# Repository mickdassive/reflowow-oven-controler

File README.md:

# reflow-firmware
firmware and hardware for a reflow oven controller. this is verry mutch a WORK IN PROGRESS.

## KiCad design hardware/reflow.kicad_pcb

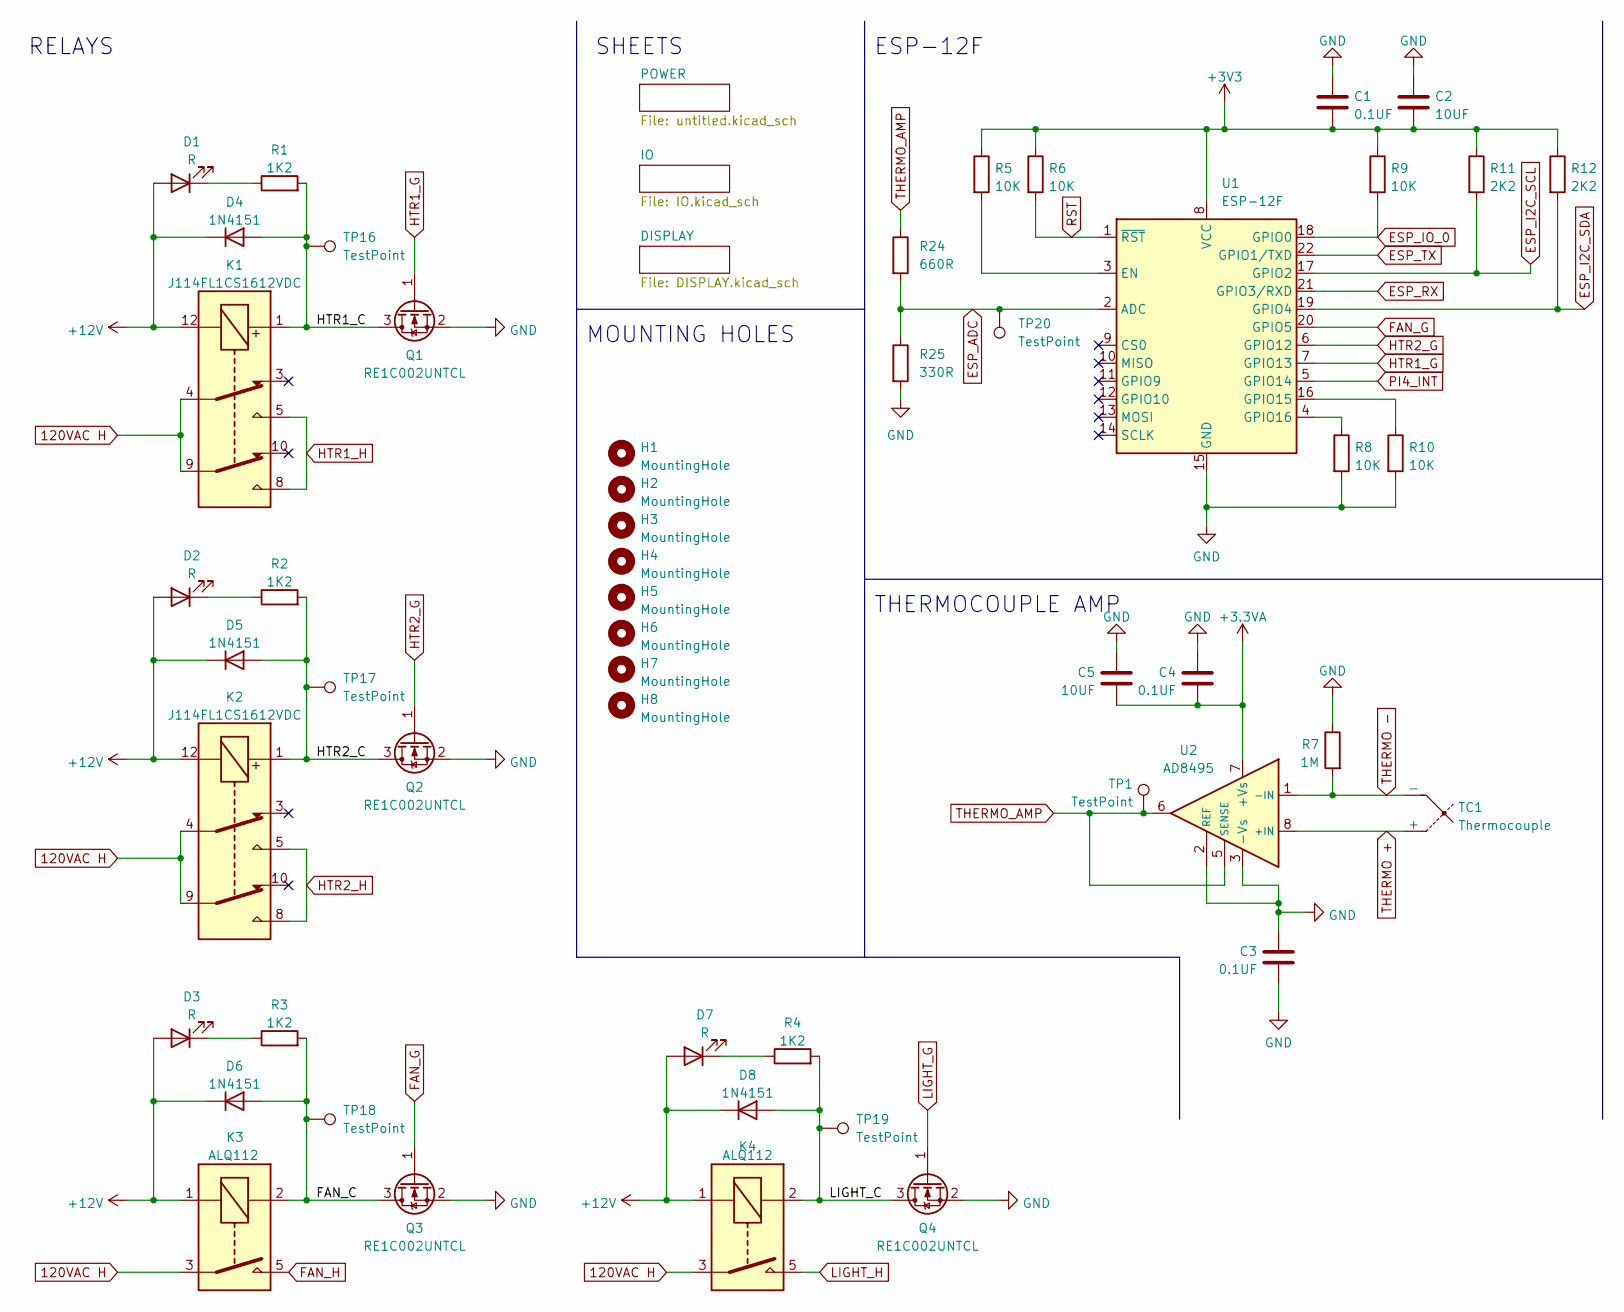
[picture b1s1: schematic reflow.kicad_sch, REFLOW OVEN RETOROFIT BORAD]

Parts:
C1, C3, C4: 0.1UF; C_0603_1608Metric
C2, C5: 10UF; C_0603_1608Metric
D1, D2, D3, D7: R; D_0603_1608Metric
D4, D5, D6, D8: 1N4151; D_0603_1608Metric
H1, H2, H3, H4, H5, H6, H7, H8: MountingHole; MountingHole_3.2mm_M3
K1, K2: J114FL1CS1612VDC
K3, K4: ALQ112; RELAY_ALQ112
Q1, Q2, Q3, Q4: RE1C002UNTCL; SOT-416
R1, R2, R3, R4: 1K2; R_0603_1608Metric
R5, R6, R8, R9, R10: 10K; R_0603_1608Metric
R7: 1M; R_0603_1608Metric
R11, R12: 2K2; R_0603_1608Metric
R24: 660R; R_0603_1608Metric
R25: 330R; R_0603_1608Metric
TC1: Thermocouple
TP1, TP16, TP17, TP18, TP19, TP20: TestPoint; TestPoint_Pad_D2.0mm
U1: ESP-12F; ESP-12E
U2: AD8495; MSOP-8_3x3mm_P0.65mm

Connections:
120VAC H: K1.4, K1.9, K2.4, K2.9, K3.3, K3.14, K4.3, K4.14; also elsewhere on the board
+3.3VA: C4.2, C5.2, U2.7 (+Vs); also elsewhere on the board
+3V3: C1.2, C2.2, R5.1, R6.1, R9.1, R11.1, R12.1, U1.8 (VCC); also elsewhere on the board
+12V: D1.2 (A), D2.2 (A), D3.2 (A), D4.1 (K), D5.1 (K), D6.1 (K), D7.2 (A), D8.1 (K), K1.12, K2.12, K3.1, K4.1; also elsewhere on the board
ESP_ADC: R24.2, R25.1, TP20.1, U1.2 (ADC)
ESP_I2C_SCL: R11.2, U1.17 (GPIO2); also elsewhere on the board
ESP_I2C_SDA: R12.2, U1.19 (GPIO4); also elsewhere on the board
ESP_IO_0: R9.2, U1.18 (GPIO0); also elsewhere on the board
ESP_RX: U1.21 (GPIO3/RXD); also elsewhere on the board
ESP_TX: U1.22 (GPIO1/TXD); also elsewhere on the board
FAN_G: Q3.1 (G), U1.20 (GPIO5)
FAN_H: K3.5, K3.8; also elsewhere on the board
HTR1_G: Q1.1 (G), U1.7 (GPIO13)
HTR1_H: K1.5, K1.8; also elsewhere on the board
HTR2_G: Q2.1 (G), U1.6 (GPIO12)
HTR2_H: K2.5, K2.8; also elsewhere on the board
LIGHT_G: Q4.1 (G); also elsewhere on the board
LIGHT_H: K4.5, K4.8; also elsewhere on the board
unnamed: D1.1 (K), R1.1
unnamed: D2.1 (K), R2.1
unnamed: D3.1 (K), R3.1
unnamed: D7.1 (K), R4.1
unnamed: R5.2, U1.3 (EN)
unnamed: R8.1, U1.4 (GPIO16)
unnamed: R10.1, U1.16 (GPIO15)
PI4_INT: U1.5 (GPIO14); also elsewhere on the board
RST: R6.2, U1.1 (~RST); also elsewhere on the board
THERMO +: TC1.1 (+), U2.8 (+IN); also elsewhere on the board
THERMO -: R7.2, TC1.2 (-), U2.1 (-IN); also elsewhere on the board
THERMO_AMP: R24.1, TP1.1, U2.5 (SENSE), U2.6

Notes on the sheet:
THERMOCOUPLE AMP
ESP-12F
SHEETS
MOUNTING HOLES
RELAYS

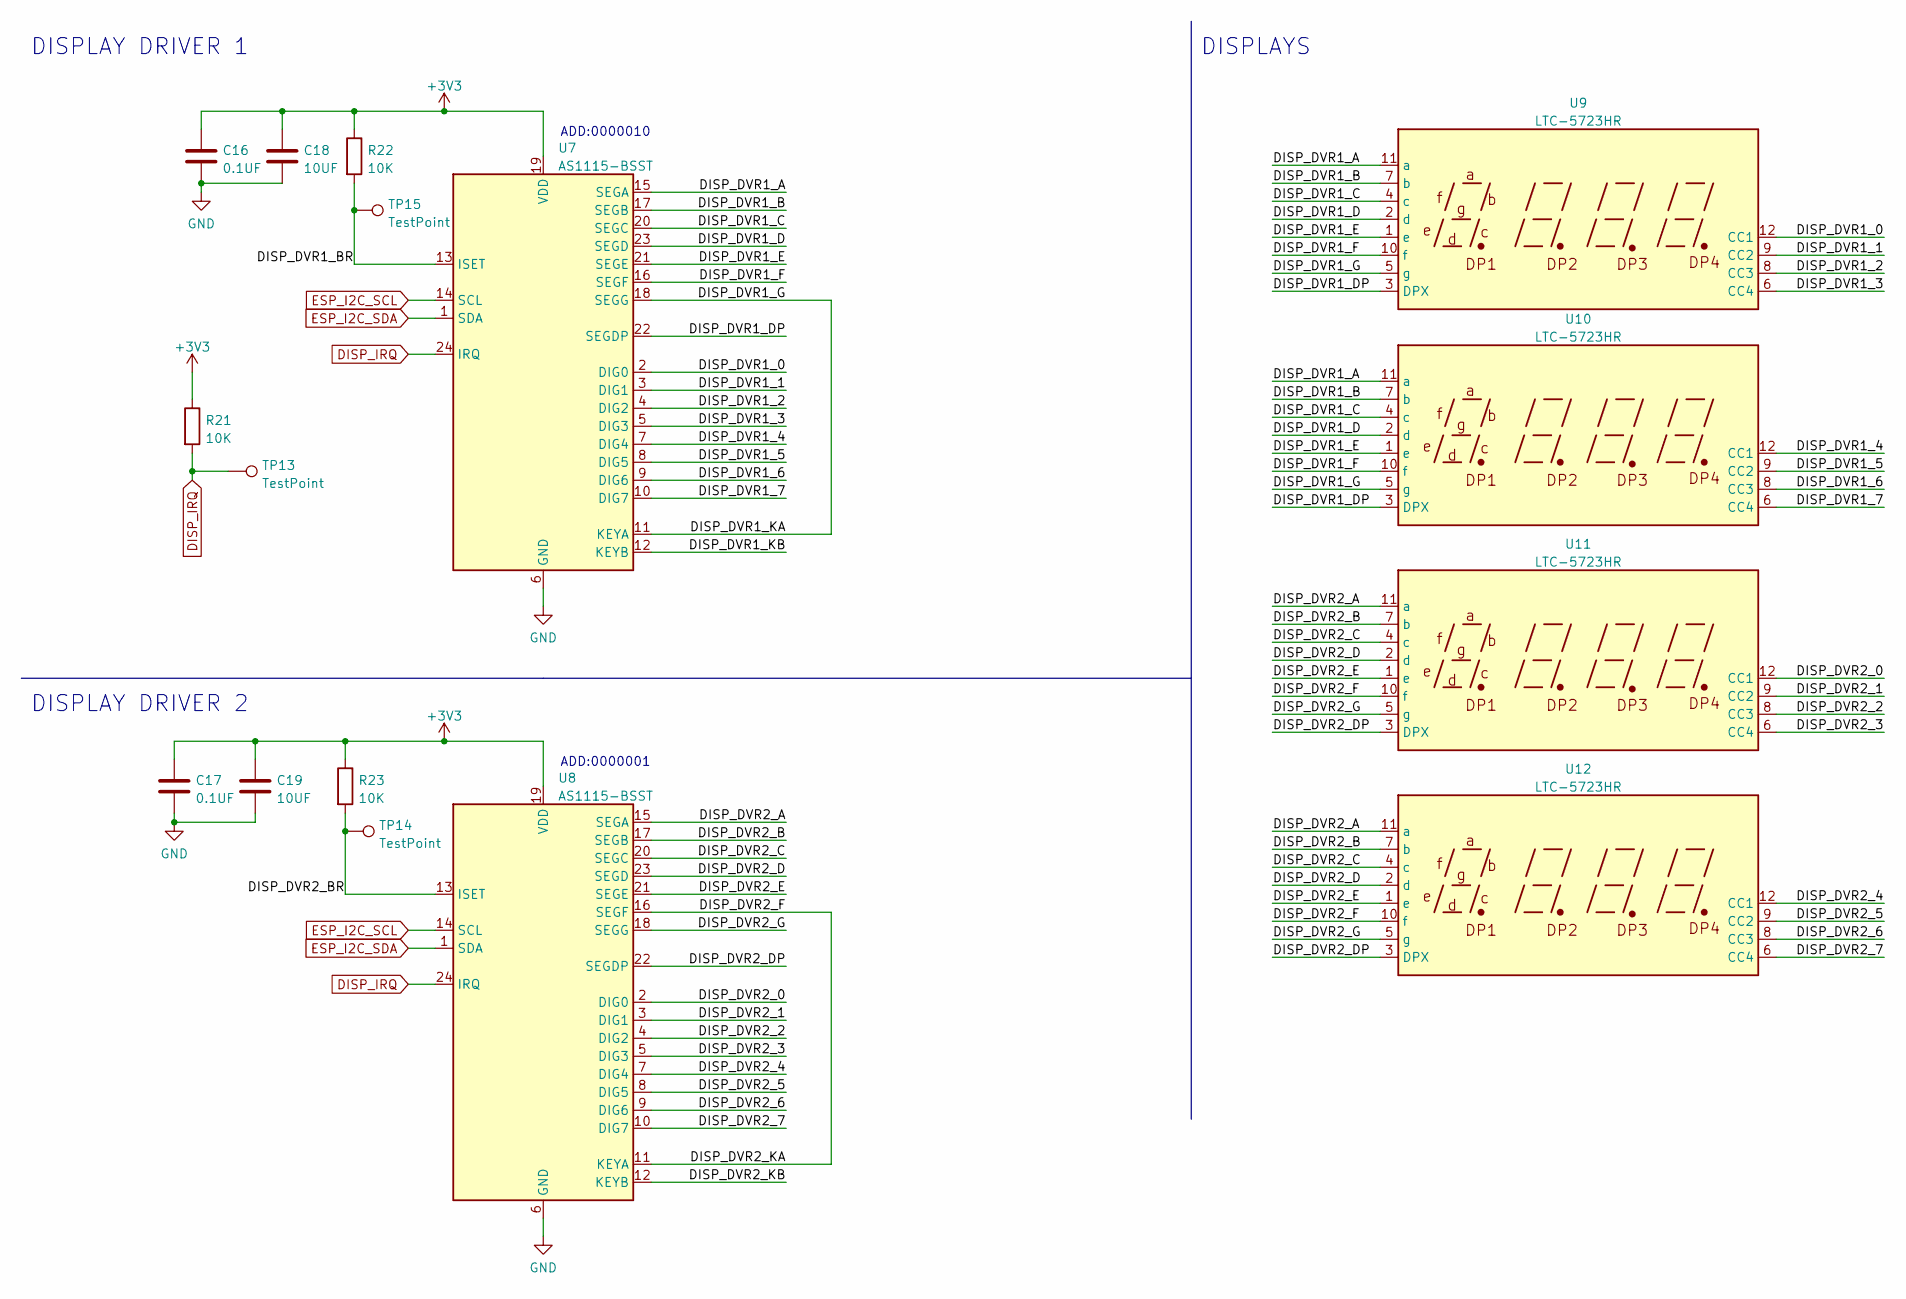
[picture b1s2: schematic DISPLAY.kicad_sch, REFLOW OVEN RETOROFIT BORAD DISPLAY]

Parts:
C16, C17: 0.1UF; C_0603_1608Metric
C18, C19: 10UF; C_0603_1608Metric
R21, R22, R23: 10K; R_0603_1608Metric
TP13, TP14, TP15: TestPoint; TestPoint_Pad_D2.0mm
U7, U8: AS1115-BSST; QSOP-24_3.9x8.7mm_P0.635mm
U9, U10, U11, U12: LTC-5723HR; CA56-12CGKWA

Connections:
+3V3: C16.1, C17.1, C18.1, C19.1, R21.1, R22.1, R23.1, U7.19 (VDD), U8.19 (VDD); also elsewhere on the board
/DISPLAY/DISP_DVR1_0: U7.2 (DIG0), U9.12 (CC1)
/DISPLAY/DISP_DVR1_1: U7.3 (DIG1), U9.9 (CC2)
/DISPLAY/DISP_DVR1_2: U7.4 (DIG2), U9.8 (CC3)
/DISPLAY/DISP_DVR1_3: U7.5 (DIG3), U9.6 (CC4)
/DISPLAY/DISP_DVR1_4: U7.7 (DIG4), U10.12 (CC1)
/DISPLAY/DISP_DVR1_5: U7.8 (DIG5), U10.9 (CC2)
/DISPLAY/DISP_DVR1_6: U7.9 (DIG6), U10.8 (CC3)
/DISPLAY/DISP_DVR1_7: U7.10 (DIG7), U10.6 (CC4)
/DISPLAY/DISP_DVR1_A: U7.15 (SEGA), U9.11 (a), U10.11 (a)
/DISPLAY/DISP_DVR1_B: U7.17 (SEGB), U9.7 (b), U10.7 (b)
/DISPLAY/DISP_DVR1_BR: R22.2, TP15.1, U7.13 (ISET)
/DISPLAY/DISP_DVR1_C: U7.20 (SEGC), U9.4 (c), U10.4 (c)
/DISPLAY/DISP_DVR1_D: U7.23 (SEGD), U9.2 (d), U10.2 (d)
/DISPLAY/DISP_DVR1_DP: U7.22 (SEGDP), U9.3 (DPX), U10.3 (DPX)
/DISPLAY/DISP_DVR1_E: U7.21 (SEGE), U9.1 (e), U10.1 (e)
/DISPLAY/DISP_DVR1_F: U7.16 (SEGF), U9.10 (f), U10.10 (f)
/DISPLAY/DISP_DVR1_G: U7.11 (KEYA), U7.18 (SEGG), U9.5 (g), U10.5 (g)
/DISPLAY/DISP_DVR1_KB: U7.12 (KEYB)
/DISPLAY/DISP_DVR2_0: U8.2 (DIG0), U11.12 (CC1)
/DISPLAY/DISP_DVR2_1: U8.3 (DIG1), U11.9 (CC2)
/DISPLAY/DISP_DVR2_2: U8.4 (DIG2), U11.8 (CC3)
/DISPLAY/DISP_DVR2_3: U8.5 (DIG3), U11.6 (CC4)
/DISPLAY/DISP_DVR2_4: U8.7 (DIG4), U12.12 (CC1)
/DISPLAY/DISP_DVR2_5: U8.8 (DIG5), U12.9 (CC2)
/DISPLAY/DISP_DVR2_6: U8.9 (DIG6), U12.8 (CC3)
/DISPLAY/DISP_DVR2_7: U8.10 (DIG7), U12.6 (CC4)
/DISPLAY/DISP_DVR2_A: U8.15 (SEGA), U11.11 (a), U12.11 (a)
/DISPLAY/DISP_DVR2_B: U8.17 (SEGB), U11.7 (b), U12.7 (b)
/DISPLAY/DISP_DVR2_BR: R23.2, TP14.1, U8.13 (ISET)
/DISPLAY/DISP_DVR2_C: U8.20 (SEGC), U11.4 (c), U12.4 (c)
/DISPLAY/DISP_DVR2_D: U8.23 (SEGD), U11.2 (d), U12.2 (d)
/DISPLAY/DISP_DVR2_DP: U8.22 (SEGDP), U11.3 (DPX), U12.3 (DPX)
/DISPLAY/DISP_DVR2_E: U8.21 (SEGE), U11.1 (e), U12.1 (e)
/DISPLAY/DISP_DVR2_F: U8.11 (KEYA), U8.16 (SEGF), U11.10 (f), U12.10 (f)
/DISPLAY/DISP_DVR2_G: U8.18 (SEGG), U11.5 (g), U12.5 (g)
/DISPLAY/DISP_DVR2_KB: U8.12 (KEYB)
DISP_IRQ: R21.2, TP13.1, U7.24 (IRQ), U8.24 (IRQ)
ESP_I2C_SCL: U7.14 (SCL), U8.14 (SCL); also elsewhere on the board
ESP_I2C_SDA: U7.1 (SDA), U8.1 (SDA); also elsewhere on the board

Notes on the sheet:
DISPLAYS
DISPLAY DRIVER 2
ADD:0000001
ADD:0000010
DISPLAY DRIVER 1

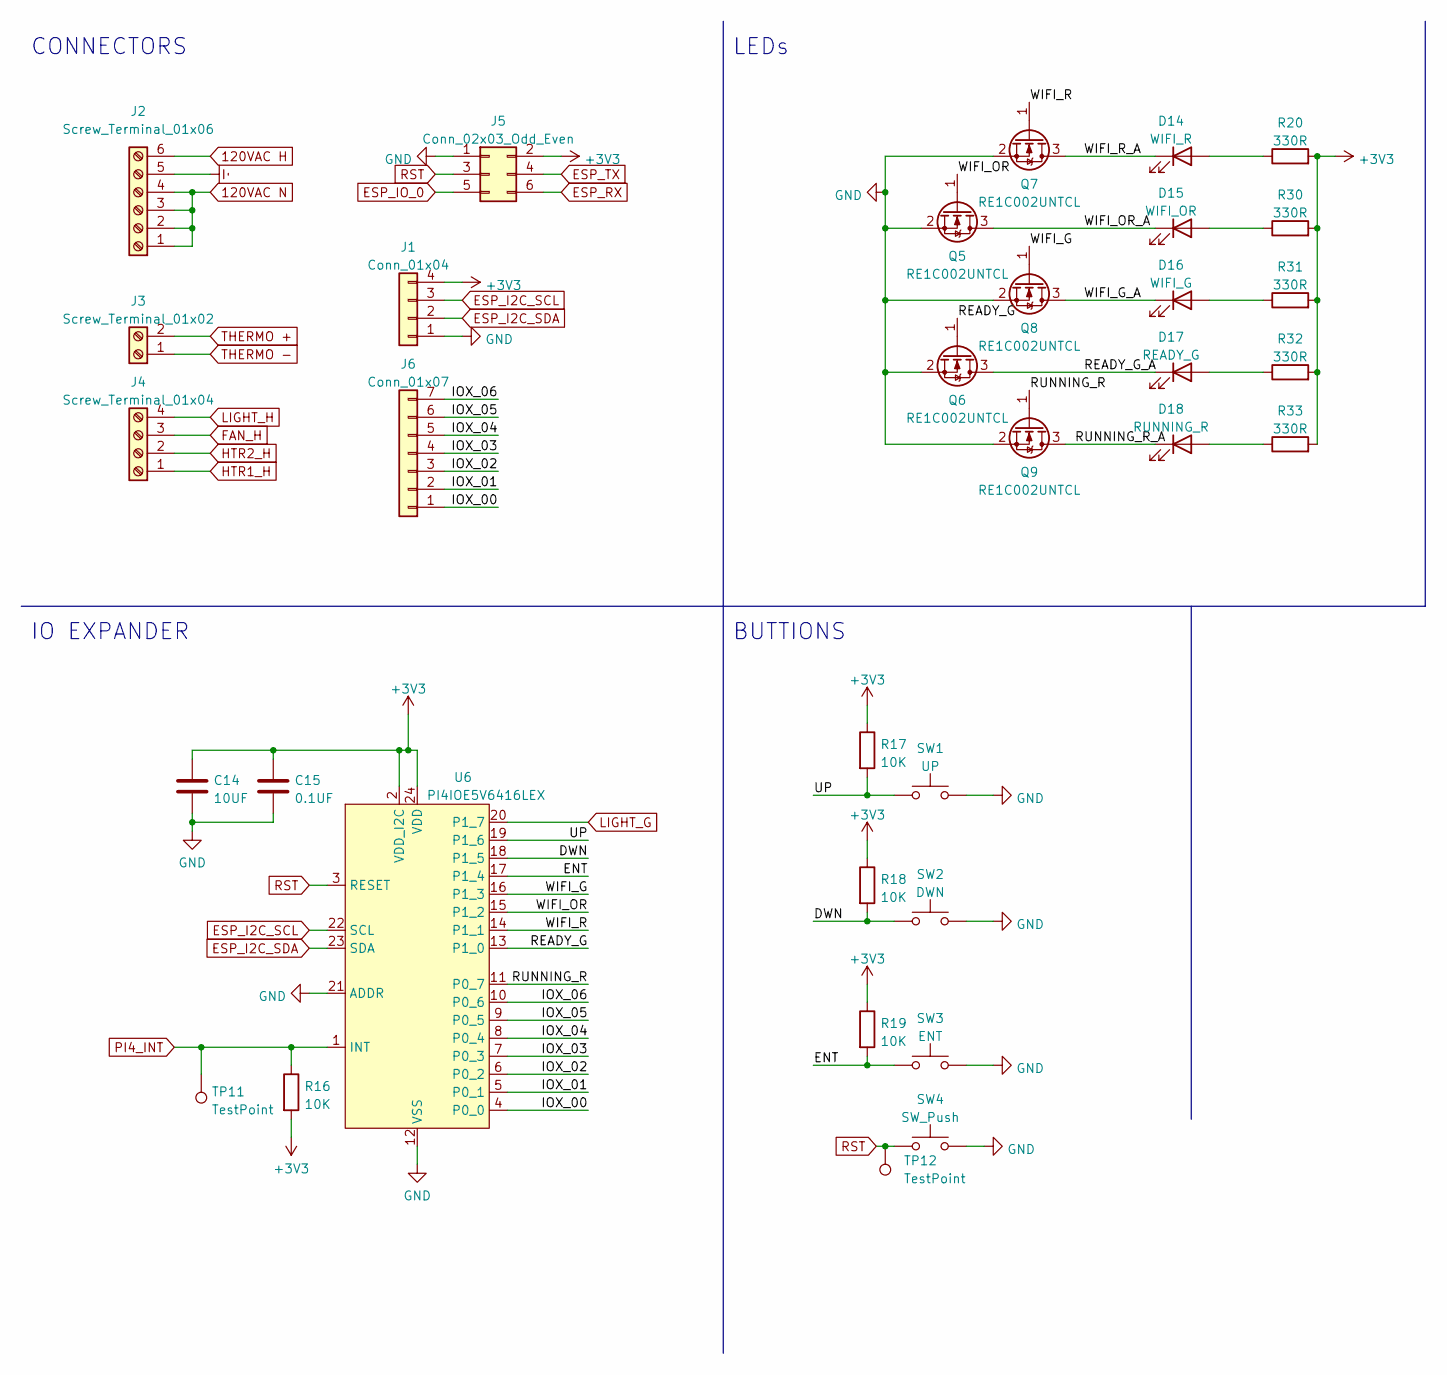
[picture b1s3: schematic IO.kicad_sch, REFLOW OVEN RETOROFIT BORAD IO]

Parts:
C14: 10UF; C_0603_1608Metric
C15: 0.1UF; C_0603_1608Metric
D14: WIFI_R; D_0603_1608Metric
D15: WIFI_OR; D_0603_1608Metric
D16: WIFI_G; D_0603_1608Metric
D17: READY_G; D_0603_1608Metric
D18: RUNNING_R; D_0603_1608Metric
J1: Conn_01x04; PinHeader_1x04_P2.54mm_Vertical
J2: Screw_Terminal_01x06; SCREW_TERM_5MM_7
J3: Screw_Terminal_01x02; SCREW_TERM_5MM_2
J4: Screw_Terminal_01x04; SCREW_TERM_5MM_4
J5: Conn_02x03_Odd_Even; PinHeader_2x03_P2.54mm_Vertical
J6: Conn_01x07; PinHeader_1x07_P2.54mm_Vertical
Q5, Q6, Q7, Q8, Q9: RE1C002UNTCL; SOT-416
R16, R17, R18, R19: 10K; R_0603_1608Metric
R20, R30, R31, R32, R33: 330R; R_0603_1608Metric
SW1: UP; SW_Cherry_MX_1.00u_PCB
SW2: DWN; SW_Cherry_MX_1.00u_PCB
SW3: ENT; SW_Cherry_MX_1.00u_PCB
SW4: SW_Push; SW_Cherry_MX_1.00u_PCB
TP11, TP12: TestPoint; TestPoint_Pad_D2.0mm
U6: PI4IOE5V6416LEX; TSSOP-24_4.4x7.8mm_P0.65mm

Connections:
120VAC H: J2.7; also elsewhere on the board
120VAC N: J2.1, J2.2, J2.3, J2.4; also elsewhere on the board
+3V3: C14.1, C15.1, J1.4, J5.2, R16.2, R17.1, R18.1, R19.1, R20.2, R30.2, R31.2, R32.2, R33.2, U6.2 (VDD_I2C), U6.24 (VDD); also elsewhere on the board
/IO/DWN: R18.2, SW2.1, U6.18 (P1_5)
/IO/ENT: R19.2, SW3.1, U6.17 (P1_4)
/IO/IOX_00: J6.1, U6.4 (P0_0)
/IO/IOX_01: J6.2, U6.5 (P0_1)
/IO/IOX_02: J6.3, U6.6 (P0_2)
/IO/IOX_03: J6.4, U6.7 (P0_3)
/IO/IOX_04: J6.5, U6.8 (P0_4)
/IO/IOX_05: J6.6, U6.9 (P0_5)
/IO/IOX_06: J6.7, U6.10 (P0_6)
/IO/READY_G: Q6.1 (G), U6.13 (P1_0)
/IO/RUNNING_R: Q9.1 (G), U6.11 (P0_7)
/IO/UP: R17.2, SW1.1, U6.19 (P1_6)
/IO/WIFI_G: Q8.1 (G), U6.16 (P1_3)
/IO/WIFI_OR: Q5.1 (G), U6.15 (P1_2)
/IO/WIFI_R: Q7.1 (G), U6.14 (P1_1)
ESP_I2C_SCL: J1.3, U6.22 (SCL); also elsewhere on the board
ESP_I2C_SDA: J1.2, U6.23 (SDA); also elsewhere on the board
ESP_IO_0: J5.5; also elsewhere on the board
ESP_RX: J5.6; also elsewhere on the board
ESP_TX: J5.4; also elsewhere on the board
Earth: J2.6
FAN_H: J4.3; also elsewhere on the board
HTR1_H: J4.1; also elsewhere on the board
HTR2_H: J4.2; also elsewhere on the board
LIGHT_G: U6.20 (P1_7); also elsewhere on the board
LIGHT_H: J4.4; also elsewhere on the board
unnamed: D14.2 (A), R20.1
unnamed: D15.2 (A), R30.1
unnamed: D16.2 (A), R31.1
unnamed: D17.2 (A), R32.1
unnamed: D18.2 (A), R33.1
PI4_INT: R16.1, TP11.1, U6.1 (INT); also elsewhere on the board
RST: J5.3, SW4.2, TP12.1, U6.3 (RESET); also elsewhere on the board
THERMO +: J3.2; also elsewhere on the board
THERMO -: J3.1; also elsewhere on the board

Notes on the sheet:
CONNECTORS
BUTTIONS
LEDs
IO EXPANDER

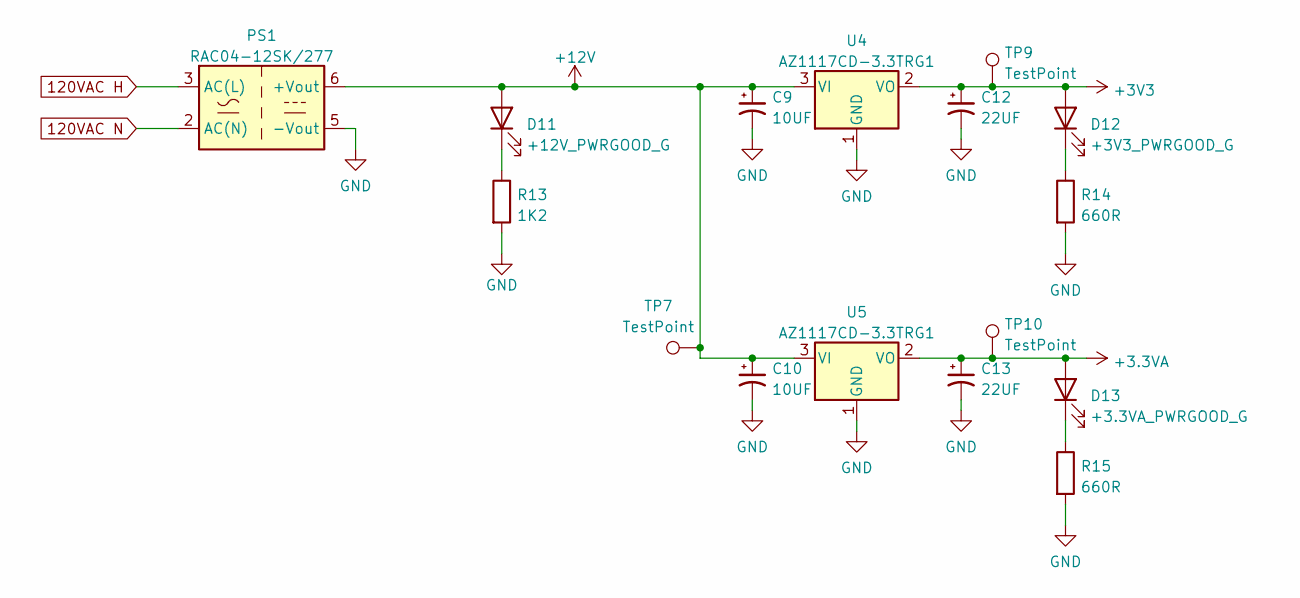
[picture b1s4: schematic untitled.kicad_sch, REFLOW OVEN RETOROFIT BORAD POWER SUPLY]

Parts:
C9, C10: 10UF; C_0603_1608Metric
C12, C13: 22UF; C_0603_1608Metric
D11: +12V_PWRGOOD_G; D_0603_1608Metric
D12: +3V3_PWRGOOD_G; D_0603_1608Metric
D13: +3.3VA_PWRGOOD_G; D_0603_1608Metric
PS1: RAC04-12SK/277; CONV_RAC04-12SK_277
R13: 1K2; R_0603_1608Metric
R14, R15: 660R; R_0603_1608Metric
TP7, TP9, TP10: TestPoint; TestPoint_Pad_D2.0mm
U4, U5: AZ1117CD-3.3TRG1; TO-252-3_TabPin2

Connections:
120VAC H: PS1.3 (AC(L)); also elsewhere on the board
120VAC N: PS1.2 (AC(N)); also elsewhere on the board
+3.3VA: C13.1, D13.2 (A), TP10.1, U5.2 (VO); also elsewhere on the board
+3V3: C12.1, D12.2 (A), TP9.1, U4.2 (VO); also elsewhere on the board
+12V: C9.1, C10.1, D11.2 (A), PS1.6 (+Vout), TP7.1, U4.3 (VI), U5.3 (VI); also elsewhere on the board
unnamed: D11.1 (K), R13.1
unnamed: D12.1 (K), R14.1
unnamed: D13.1 (K), R15.1

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
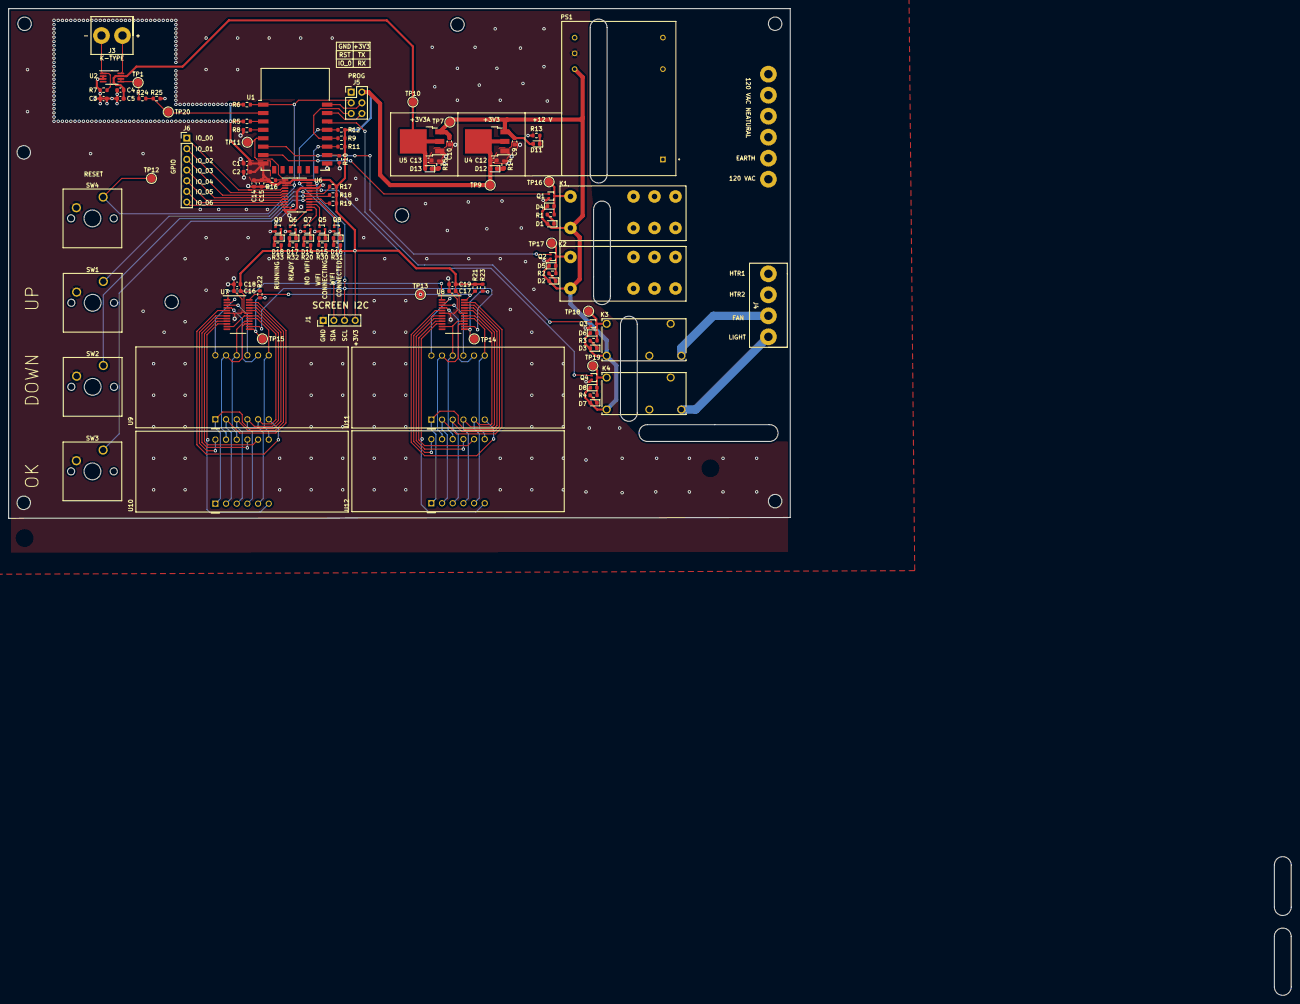
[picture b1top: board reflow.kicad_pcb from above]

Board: 2 copper layers, 186.0 x 121.3 mm, 117 parts (1 on the bottom side), 99 nets.

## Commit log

2023-01-10 added kicad filles for hardware
2023-01-10 Create LICENSE
2023-01-10 updated kicad files
2023-01-10 added gpl3 headder
2023-01-10 minor adjustments to main
2023-01-10 added more commenting and some minor changes to reflow loop
2023-01-10 minor changes
2023-01-10 updated hardware schimatics for better readability
2023-01-12 adjusted the pid fuction
2023-01-16 refreshed html ibom
2023-01-16 trubeel shooting
2023-01-16 added a voltage devider to the input of the esp. and minor code refactoring to match
2023-01-16 added a voltage devider for the dcinput on the esp
2023-01-16 more hardware revisions
2023-01-17 middel of trubbelshooting super messy rn
2023-01-19 still trubbelshooting
2023-01-19 trubbelshooting
2023-01-19 minor hardware refactoring
2023-01-19 testing still
2023-01-20 tubbelhooting finaly got some rudimentry i2c working
2023-01-20 minor hardware refactroing
2023-01-20 code refarctoring
2023-01-20 remande the vs code workspace
2023-01-20 re-writen the the io_call fuction
2023-02-12 finaly got the io_call fuction working
2023-02-13 fianly got the dsip_write fuction working
2023-02-13 reabsed the menusystem still not stisfyued
2023-02-14 got decimal points in disp_write fuction to work correctly
2023-02-14 testing and refineing
2023-02-14 added a boot animation
2023-02-16 minor hardware refactoring & added firmware fuction
2023-03-03 major hardware refctoring to use modern parts that are still being made
2023-03-05 minmor testing
2023-04-06 cleaned up code a bit
2023-04-09 minor cleanup
2023-05-20 added QOL features
2023-05-21 adjusted reflow controll loop to use both time and temp dependant insted of only time
2023-05-21 currently in the middel of refactoring the reflow loop
2023-05-21 adusted reflow controll loop
2025-05-28 reworked and organised
